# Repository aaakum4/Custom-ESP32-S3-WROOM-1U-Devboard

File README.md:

# ESP32-S3 Devboard Project
This is my custom ESP32-S3-WROOM-1U devboard project. I loosely followed Kai’s guide, but made a bunch of changes along the way to fit the ESP32-S3 and to learn more about PCB design. The board includes USB-C power, a MicroSD slot, UART, JTAG, reset/boot buttons, and an I²C connector — plus some custom Gojo artwork because why not.

## BOM (Initial Planning)
- 2.4GHz antenna (https://www.ebay.com.au/itm/227057783591?chn=ps&_ul=AU&var=526207835011&_trkparms=ispr%3D1&amdata=enc%3A1JqkfGHxeTHa0H-Di2HTCtg9&norover=1&mkevt=1&mkrid=705-173151-935305-0&mkcid=2&mkscid=101&itemid=526207835011_227057783591&targetid=2367800370202&device=c&mktype=pla&googleloc=9071804&poi=&campaignid=21776442415&mkgroupid=173963205248&rlsatarget=pla-2367800370202&abcId=10047386&merchantid=7364522&gad_source=4&gad_campaignid=21776442415&gbraid=0AAAAAD97CxTGD4XsnoSlA3ppn-XnAxOJF&gclid=Cj0KCQiArt_JBhCTARIsADQZayk99jP863GEzN5mpCXxC3UyToZESEXPnro-gabtJ7L_-CaUlK0EnMoaAhjtEALw_wcB)

- Touch Screen (https://core-electronics.com.au/2-8-tft-display-240x320-with-capacitive-touchscreen.html)
A possible later addition

- USB-C Power (https://jlcpcb.com/partdetail/Korean_HropartsElec-TYPE_C_31_M12/C165948)

- Switch (https://jlcpcb.com/partdetail/XUNPU-TS_1088AR02016/C720477)

- https://www.arrow.com/en/products/1040310811/molex?utm_source=chatgpt.com

- https://core-electronics.com.au/male-pin-header-2-54mm-1x40.html

** Note much of these aren't used, but I thought I'd leave them here in-case anybody wants to do a similar project, here are some ideas.

## Bill of Materials (BOM)

** This list is by no means perfect.

## Development Journal
Here’s the whole journey from start to finish.

## Researching Devboards
Before I even started, I had to figure out what a devboard actually is and what they’re used for. I knew I wanted to make my own, but I didn’t know much beyond that.
I spent a while reading, asking ChatGPT questions, and checking out examples online. I also made a plan for how my board would differ from the guide.

## Power System & USB-C
I started wiring up the power section first. At one point I went down the rabbit hole of trying to use a buck switching regulator, but eventually realised I was overcomplicating things.
So I scrapped that and switched to the MCP1700 LDO instead — way simpler and fits the project better.

## First Schematic Pass
Once I switched to the ESP32-S3 (instead of the RP2040 used in the guide), things got a lot more complicated. The datasheet helped, but there were still a ton of questions.
With help from Slack and ChatGPT, I put together the first full version of the schematic. Definitely not perfect, but it was a solid starting point.

## Finalising the Schematic
After some feedback from Reddit, I made a bunch of improvements and finally wrapped the schematic up.
At this point the board had everything I wanted: USB-C, MicroSD, UART, JTAG, reset/boot buttons, and I²C.
The hardest part was honestly just knowing whether what I did was correct, but the community feedback helped a ton.

## Footprint Assignment
Assigning footprints was next. Most were easy thanks to the guide, but a couple (like the MicroSD slot and ferrite bead) weren’t.
After some datasheet hunting, I got them sorted out without too much trouble.

## Organising Components
This part was surprisingly fun. At first I felt overwhelmed by the wall of random capacitors and resistors, but after spending a bit of time on it everything started to make sense.

## Routing + Adding Artwork
Routing took forever — easily the longest part. This is only the second PCB I’ve ever routed, so I spent a lot of time learning and undoing mistakes.
Two big things I learned:
- USB D+ and D− need to be the same length
- MicroSD lines should avoid vias if possible
After a bunch of restarts and hours of routing, I finally got it into a place I’m happy with.
** Note: A good peice of advice I got from Kai's guide was to not route ground and instead do a ground fill, this saved alot of time and actally looks really nice.
I also added Gojo artwork on the front and back because the board needed some personality.
Another important part was removing alot of the labeling like 'C6' for capacitor 6, it makes the board look alot cleaner.

## Creating the Production ZIP
Before exporting anything, I did a full DRC check and gave the whole PCB a final look over.
The Gerbers and drill files exported fine, but the BOM and footprint position files needed their headers renamed so the manufacturer will accept them:
Footprint Position Fixes
- Ref → Designator
- PosX → Mid X
- PosY → Mid Y
- Rot → Rotation
- Side → Layer

BOM Fix
- Designation → Comment

After fixing those, I zipped everything up into a production-ready file.

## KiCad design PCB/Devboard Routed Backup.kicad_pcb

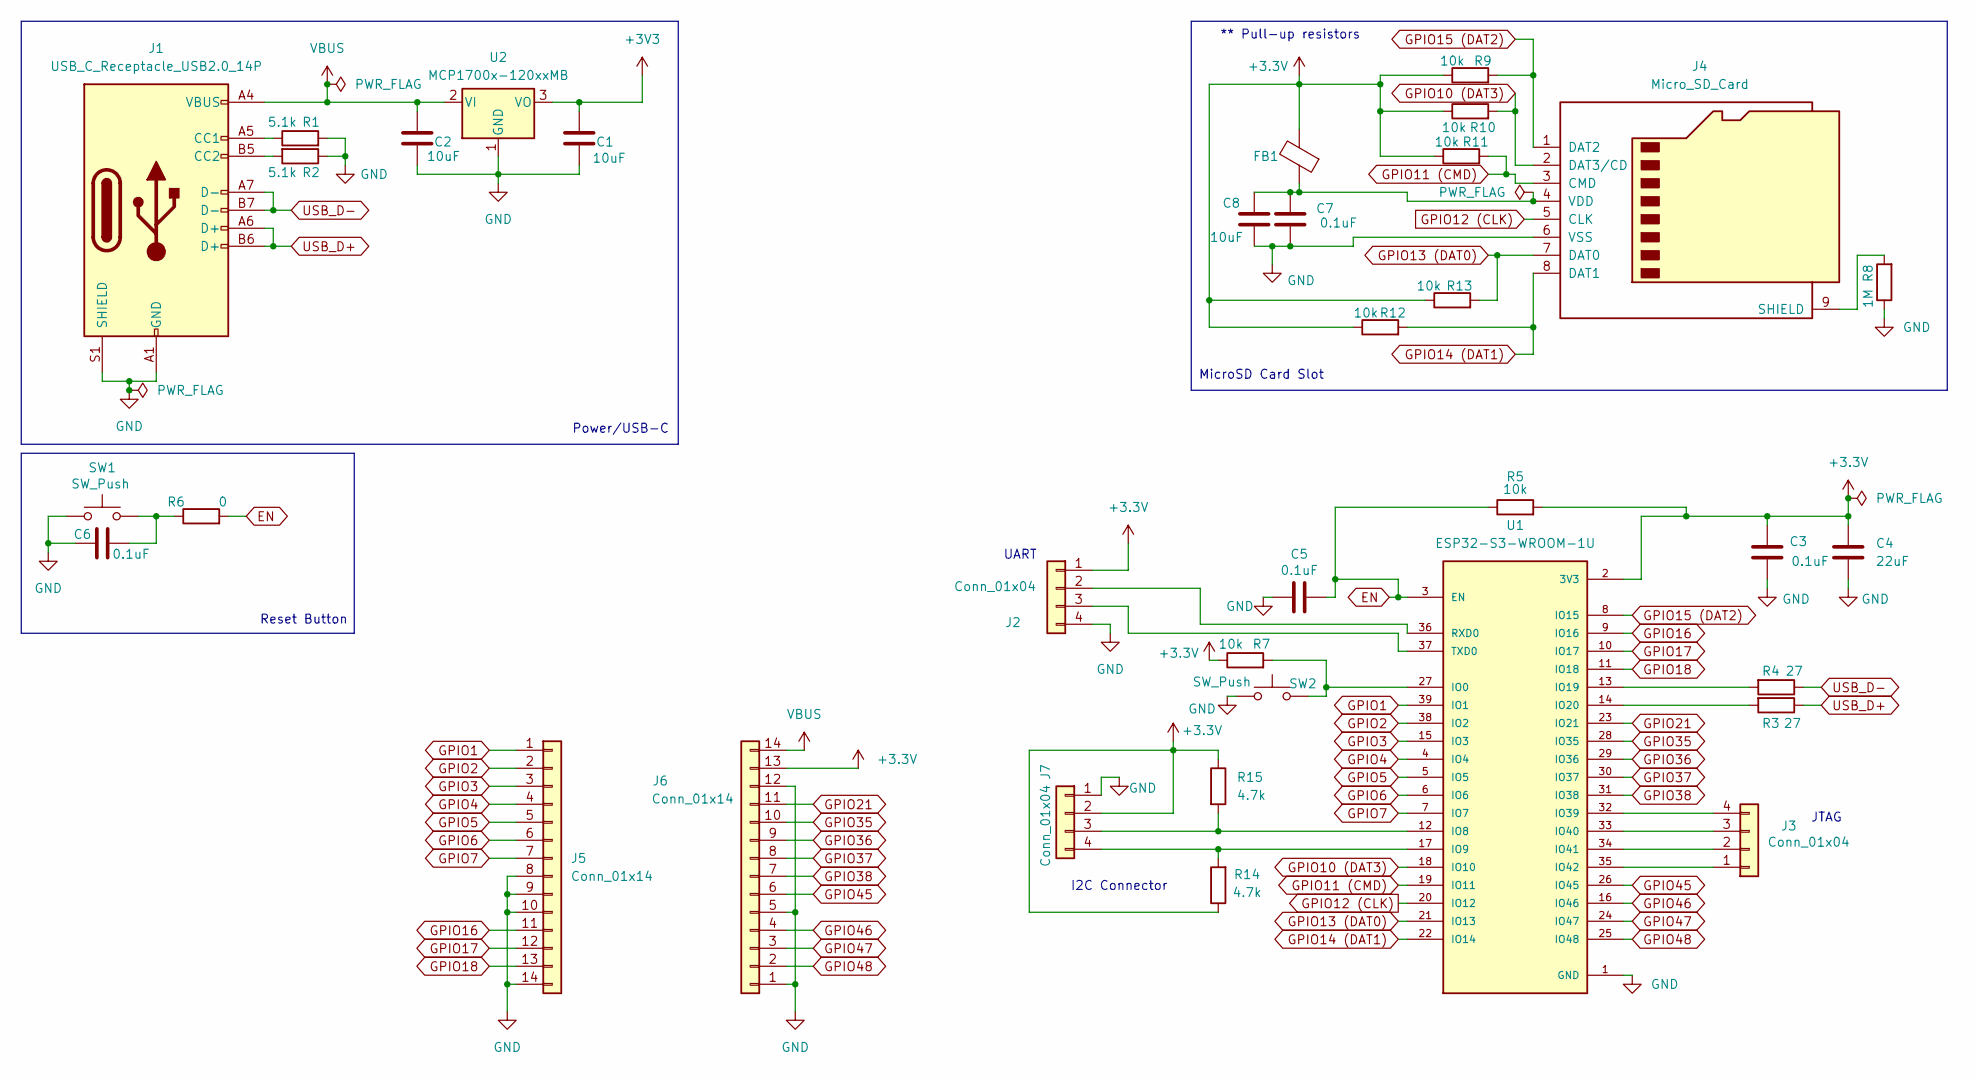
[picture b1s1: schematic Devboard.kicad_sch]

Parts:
C1, C2, C8: 10uF; C_0603_1608Metric
C3, C5, C6, C7: 0.1uF; C_0402_1005Metric
C4: 22uF; C_0603_1608Metric
FB1: FerriteBead; L_Walsin_WLFM201209x
J1: USB_C_Receptacle_USB2.0_14P; USB_C_Receptacle_HRO_TYPE-C-31-M-12
J2, J3: Conn_01x04; PinHeader_1x04_P2.54mm_Vertical
J4: Micro_SD_Card; microSD_HC_Molex_104031-0811
J5, J6: Conn_01x14; PinHeader_1x14_P2.54mm_Vertical
J7: Conn_01x04; JST_SH_SM04B-SRSS-TB_1x04-1MP_P1.00mm_Horizontal
R1, R2: 5.1k; R_0402_1005Metric
R3, R4: 27; R_0402_1005Metric
R5, R7, R9, R10, R11, R12, R13: 10k; R_0402_1005Metric
R6: 0; R_0402_1005Metric
R8: 1M; R_0603_1608Metric
R14, R15: 4.7k; R_0402_1005Metric
SW1, SW2: SW_Push; SW_Push_SPST_NO_Alps_SKRK
U1: ESP32-S3-WROOM-1U; PARTREV v0.6
U2: MCP1700x-120xxMB; SOT-89-3

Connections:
+3.3V: C3.1, C4.1, FB1.2, J2.1, J6.13, J7.2, R5.2, R7.1, R9.1, R10.1, R11.1, R12.1, R13.1, R14.1, R15.1, U1.2 (3V3)
+3V3: C1.1, U2.3 (VO)
EN: C5.2, R5.1, R6.2, U1.3 (EN)
GND: C1.2, C2.2, C3.2, C4.2, C5.1, C6.1, C7.1, C8.2, J1.A1 (GND), J1.A12 (GND), J1.B1 (GND), J1.B12 (GND), J1.S1 (SHIELD), J2.4, J4.6 (VSS), J5.8, J5.9, J5.10, J5.14, J6.1, J6.5, J6.12, J7.1, R1.2, R2.1, R8.1, SW1.1, SW2.1, U1.1 (GND), U1.40 (GND), U1.41_1 (GND), U1.41_2 (GND), U1.41_3 (GND), U1.41_4 (GND), U1.41_5 (GND), U1.41_6 (GND), U1.41_7 (GND), U1.41_8 (GND), U1.41_9 (GND), U2.1 (GND)
GPIO1: J5.1, U1.39 (IO1)
GPIO2: J5.2, U1.38 (IO2)
GPIO3: J5.3, U1.15 (IO3)
GPIO4: J5.4, U1.4 (IO4)
GPIO5: J5.5, U1.5 (IO5)
GPIO6: J5.6, U1.6 (IO6)
GPIO7: J5.7, U1.7 (IO7)
GPIO10 (DAT3): J4.2 (DAT3/CD), R10.2, U1.18 (IO10)
GPIO11 (CMD): J4.3 (CMD), R11.2, U1.19 (IO11)
GPIO12 (CLK): J4.5 (CLK), U1.20 (IO12)
GPIO13 (DAT0): J4.7 (DAT0), R13.2, U1.21 (IO13)
GPIO14 (DAT1): J4.8 (DAT1), R12.2, U1.22 (IO14)
GPIO15 (DAT2): J4.1 (DAT2), R9.2, U1.8 (IO15)
GPIO16: J5.11, U1.9 (IO16)
GPIO17: J5.12, U1.10 (IO17)
GPIO18: J5.13, U1.11 (IO18)
GPIO21: J6.11, U1.23 (IO21)
GPIO35: J6.10, U1.28 (IO35)
GPIO36: J6.9, U1.29 (IO36)
GPIO37: J6.8, U1.30 (IO37)
GPIO38: J6.7, U1.31 (IO38)
GPIO45: J6.6, U1.26 (IO45)
GPIO46: J6.4, U1.16 (IO46)
GPIO47: J6.3, U1.24 (IO47)
GPIO48: J6.2, U1.25 (IO48)
unnamed: C6.2, R6.1, SW1.2
unnamed: J1.A5 (CC1), R1.1
unnamed: J1.B5 (CC2), R2.2
unnamed: J2.2, U1.36 (RXD0)
unnamed: J2.3, U1.37 (TXD0)
unnamed: J3.1, U1.35 (IO42)
unnamed: J3.2, U1.34 (IO41)
unnamed: J3.3, U1.33 (IO40)
unnamed: J3.4, U1.32 (IO39)
unnamed: J4.9 (SHIELD), R8.2
unnamed: C7.2, C8.1, FB1.1, J4.4 (VDD)
unnamed: J7.3, R15.2, U1.12 (IO8)
unnamed: J7.4, R14.2, U1.17 (IO9)
unnamed: R7.2, SW2.2, U1.27 (IO0)
unnamed: R4.2, U1.13 (IO19)
unnamed: R3.2, U1.14 (IO20)
USB_D+: J1.A6 (D+), J1.B6 (D+), R3.1
USB_D-: J1.A7 (D-), J1.B7 (D-), R4.1
VBUS: C2.1, J1.A4 (VBUS), J1.A9 (VBUS), J1.B4 (VBUS), J1.B9 (VBUS), J6.14, U2.2 (VI)

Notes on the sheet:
I2C Connector
** Pull-up resistors
Reset Button
Power/USB-C
JTAG
UART
MicroSD Card Slot

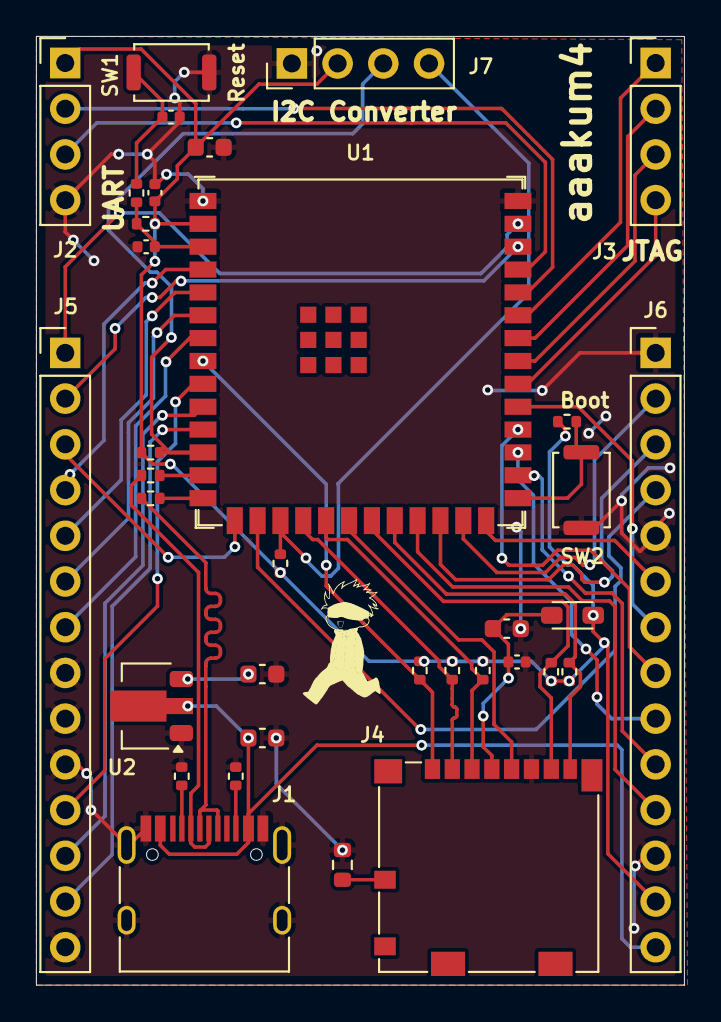
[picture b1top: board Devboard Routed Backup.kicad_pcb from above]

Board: 2 copper layers, 36.0 x 52.7 mm, 35 parts (0 on the bottom side), 48 nets.

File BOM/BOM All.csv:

BOM Table,,,,,,,,,,,,,,,,,
JLCPCB BOM Tool - BOM Matching,,,,,,,,,,,,,,,,,
BOM name_Devboard Routed Backup-JLCPCB Assembly Order.xlsx,,,Download Time_2025-12-13 15:56:26,,,,"* Our matching results are updated in real-time, but stock and prices may change. 
If it's been over 24 hours, please re-match before placing your order.",,,,,,,,,,
PCB Assembled Qty_5,,,Est. Total Price_3.9206,,,,,,,,,,,,,,
Your BOM,,,,,Matched Parts,,,,,,,Order Information,,,,,
Top Designator,Bottom Designator,Comment,Footprint,JLCPCB Part #,Matches,Part # ,Manufacturer,Footprint,Description,Category,Warning,JLCPCB Part #,Product link,Lib Type,Qty,Source,Total Price ($)
"C3,C5,C7,C6",,0.1uF,C_0402_1005Metric,,Select by Customer,CL05B104KO5NNNC,Samsung Electro-Mechanics,402,100nF 16V X7R ±10% 0402 Multilayer Ceramic Capacitors MLCC - SMD/SMT ROHS,Multilayer Ceramic Capacitors MLCC - SMD/SMT,1.The comment (CL05B104KO5NNNC) of this part does not match the one (0.1uF) provided in your BOM. Please confirm;,C1525,https://jlcpcb.com/partdetail/1877-CL05B104KO5NNNC/C1525,Basic,8,8 JLCPCB,0.0096
C4,,22uF,C_0603_1608Metric,,Select by Customer,CL10A226MP8NUNE,Samsung Electro-Mechanics,603,10V 22uF X5R ±20% 0603 Multilayer Ceramic Capacitors MLCC - SMD/SMT ROHS,Multilayer Ceramic Capacitors MLCC - SMD/SMT,,C86295,https://jlcpcb.com/partdetail/87471-CL10A226MP8NUNE/C86295,Extended,20,20 JLCPCB,0.288
"C8,C2,C1",,10uF,C_0603_1608Metric,,Select by Customer,CL10A106KP8NNNC,Samsung Electro-Mechanics,603,10V 10uF X5R ±10% 0603 Multilayer Ceramic Capacitors MLCC - SMD/SMT ROHS,Multilayer Ceramic Capacitors MLCC - SMD/SMT,,C19702,https://jlcpcb.com/partdetail/20411-CL10A106KP8NNNC/C19702,Basic,6,6 JLCPCB,0.0336
FB1,,FerriteBead,L_Walsin_WLFM201209x,,Select by Customer,BLM21PG221SN1D,Murata Electronics,805,1 220½@100MHz 2A 45m½ ±25% 0805 Ferrite Beads ROHS,Ferrite Beads,,C85840,https://jlcpcb.com/partdetail/MurataElectronics-BLM21PG221SN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,Extended,20,20 JLCPCB,0.316
J1,,USB_C_Receptacle_USB2.0_14P,USB_C_Receptacle_HRO_TYPE-C-31-M-12,,Select by Customer,TYPE-C-31-M-12,Korean Hroparts Elec,SMD,1 16P 5A Female Type-C SMD USB Connectors ROHS,USB Connectors,,C165948,https://jlcpcb.com/partdetail/Korean_HropartsElec-TYPE_C_31_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,Extended,2,2 JLCPCB,0.3388
"J3,J7,J2",,Conn_01x04,PinHeader_1x04_P2.54mm_Vertical,,Select by Customer,2.54-1*40P__,BOOMELE(Boom Precision Elec),"__,P=2.54mm","-25_~+85_ 1 1x40P 2.54mm 2.5mm 3A 3mm 40P 6mm Black Brass Gold Pin Header Through Hole Plugin,P=2.54mm Pin Headers ROHS",Pin Headers,1.Multiple lines in the BOM have been matched to the same part. Please check if the matching is correct. ;,C2337,https://jlcpcb.com/partdetail/2712-2_54_1_40P/C2337,Extended,0,0 JLCPCB,0
"J6,J5",,Conn_01x14,PinHeader_1x14_P2.54mm_Vertical,,Select by Customer,2.54-1*40P__,BOOMELE(Boom Precision Elec),"__,P=2.54mm","-25_~+85_ 1 1x40P 2.54mm 2.5mm 3A 3mm 40P 6mm Black Brass Gold Pin Header Through Hole Plugin,P=2.54mm Pin Headers ROHS",Pin Headers,1.Multiple lines in the BOM have been matched to the same part. Please check if the matching is correct. ;,C2337,https://jlcpcb.com/partdetail/2712-2_54_1_40P/C2337,Extended,0,0 JLCPCB,0
J4,,Micro_SD_Card,microSD_HC_Molex_104031-0811,,Select by Customer,473521001,MOLEX,SMD,-40_~+85_ Connector and Ejector MicroSD Card (TF Card) Push-Push SMD SD Card / Memory Card Connector ROHS,SD Card / Memory Card Connector,,C293569,https://jlcpcb.com/partdetail/MOLEX-473521001/C293569,Extended,2,2 JLCPCB,1.869
"R2,R1",,5.1k,R_0402_1005Metric,,Select by Customer,0402WGF5101TCE,UNI-ROYAL(Uniroyal Elec),402,-55_~+155_ 5.1k½ 50V 62.5mW Thick Film Resistor ±1% ±100ppm/_ 0402 Chip Resistor - Surface Mount ROHS,Chip Resistor - Surface Mount,,C25905,https://jlcpcb.com/partdetail/26648-0402WGF5101TCE/C25905,Basic,4,4 JLCPCB,0.002
"R4,R3",,27,R_0402_1005Metric,,Select by Customer,0402WGF270JTCE,UNI-ROYAL(Uniroyal Elec),402,-55_~+155_ 27½ 50V 62.5mW Thick Film Resistor ±1% ±100ppm/_ 0402 Chip Resistor - Surface Mount ROHS,Chip Resistor - Surface Mount,1.The comment (0402WGF270JTCE) of this part does not match the one (27) provided in your BOM. Please confirm;,C25100,https://jlcpcb.com/partdetail/25843-0402WGF270JTCE/C25100,Extended,20,20 JLCPCB,0.012
"R5,R9,R10,R11,R12,R13,R7",,10k,R_0402_1005Metric,,Select by Customer,0402WGF1002TCE,UNI-ROYAL(Uniroyal Elec),402,-55_~+155_ 10k½ 50V 62.5mW Thick Film Resistor ±1% ±100ppm/_ 0402 Chip Resistor - Surface Mount ROHS,Chip Resistor - Surface Mount,1.The comment (0402WGF1002TCE) of this part does not match the one (10k) provided in your BOM. Please confirm;,C25744,https://jlcpcb.com/partdetail/26487-0402WGF1002TCE/C25744,Basic,14,14 JLCPCB,0.007
R6,,0,R_0402_1005Metric,,Select by Customer,PA0402-R-070RL,YAGEO,402,-55_~+125_ 0½ 62.5mW ±150ppm/_ 0402 Chip Resistor - Surface Mount ROHS,Chip Resistor - Surface Mount,1.The comment (PA0402-R-070RL) of this part does not match the one (0) provided in your BOM. Please confirm;,C4044221,https://jlcpcb.com/partdetail/YAGEO-PA0402_R070RL/C4044221,Extended,5,5 JLCPCB,0.642
R8,,1M,R_0603_1608Metric,,Select by Customer,0603WAF1004T5E,UNI-ROYAL(Uniroyal Elec),603,-55_~+155_ 100mW 1M½ 75V Thick Film Resistor ±1% ±100ppm/_ 0603 Chip Resistor - Surface Mount ROHS,Chip Resistor - Surface Mount,1.The comment (0603WAF1004T5E) of this part does not match the one (1M) provided in your BOM. Please confirm;,C22935,https://jlcpcb.com/partdetail/23662-0603WAF1004T5E/C22935,Basic,2,2 JLCPCB,0.0022
"R15,R14",,4.7k,R_0402_1005Metric,,Select by Customer,0402WGF470JTCE,UNI-ROYAL(Uniroyal Elec),402,-55_~+155_ 47½ 50V 62.5mW Thick Film Resistor ±1% ±100ppm/_ 0402 Chip Resistor - Surface Mount ROHS,Chip Resistor - Surface Mount,1.The comment (0402WGF470JTCE) of this part does not match the one (4.7k) provided in your BOM. Please confirm;,C25118,https://jlcpcb.com/partdetail/25861-0402WGF470JTCE/C25118,Extended,20,20 JLCPCB,0.012
"SW1,SW2",,SW_Push,SW_Push_SPST_NO_Alps_SKRK,,Select by Customer,TS-1088-AR02016,XUNPU,"SMD,4x3mm","-30_~+80_ 1.6N 100,000 Cycles 12V 2mm 3mm 4mm 50mA Black Round Button SMD(SMT) Tab SPST Surface Mount,Vertical Without Bracket SMD,4x3mm Tactile Switches ROHS",Tactile Switches,,C720477,https://jlcpcb.com/partdetail/XUNPU-TS_1088AR02016/C720477,Basic,4,4 JLCPCB,0.17
U1,,ESP32-S3-WROOM-1U,ESP32-S3-WROOM-1U,,Select by Customer,ESP32-S3-WROOM-1U-N8,Espressif Systems,"SMD,19.2x18mm","-40_~+85_ -98.2dBm 2.4GHz 20.5dBm 355mA 3V~3.6V 95mA Bluetooth5.0 ESP32-S3 UART SMD,19.2x18mm WiFi Modules ROHS",WiFi Modules,,C2980297,https://jlcpcb.com/partdetail/3401549-ESP32_S3_WROOM_1UN8/C2980297,Extended,0,0 JLCPCB,0
U2,,MCP1700x-120xxMB,SOT-89-3,,Select by Customer,HT7533-1,Holtek Semicon,SOT-89-3,"-40_~+85_@(Ta) 1 100mA 2.5uA 25mV@(1mA) 3.3V 30V Fixed Positive SOT-89-3 Voltage Regulators - Linear, Low Drop Out (LDO) Regulators ROHS","Voltage Regulators - Linear, Low Drop Out (LDO) Regulators",,C14289,https://jlcpcb.com/partdetail/HoltekSemicon-HT75331/C14289,Basic,2,2 JLCPCB,0.2184

JLCPCB Part,Layers,Dimensions,QTY,Thickness,Cost
PCB Board,2 Layers,36 mm* 52.7 mm,5,1.6mm,$2.00

EBay Part,Comment,QTY,Cost
Antenna,2.4GHz Antenna with U.FL Connector,1,AU $7.01 USD $4.67
1x40 Pin Header Breakaways,10pcs 1x40pin 2.54mm Male PCB Single Row Straight Header Strip Connector ,1,AU $6.48 USD $4.31

LCSC Part,Comment,QTY,Cost (Before shipping),Cost (After shipping)
ESP32-S3-Wroom-1U-N8,ESP32-S3-WROOM-1U-N8 2.4GHz ESP32-S3 -98.2dBm SMD,2, USD $9.34,USD $21.06

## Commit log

2025-12-09 Update README with initial BOM for Devboard
    Added initial BOM items with links for components.
2025-12-09 Fix formatting of BOM item in README
2025-12-11 Fix tactile switch link in README
    Updated link for the tactile switch in the BOM section.
2025-12-11 Update BOM section with new components and links
    Added additional components to the BOM section with links.
2025-12-12 Add new product links to README
2025-12-12 Revise README for ESP32-S3 Devboard project
    Updated project description and added sections for development journal and research.
2025-12-12 Enhance README with development journey and BOM
    Updated README to include additional sections and images detailing the development process.
2025-12-12 Added relevant files
2025-12-13 Added BOM
2025-12-13 Updated BOM
